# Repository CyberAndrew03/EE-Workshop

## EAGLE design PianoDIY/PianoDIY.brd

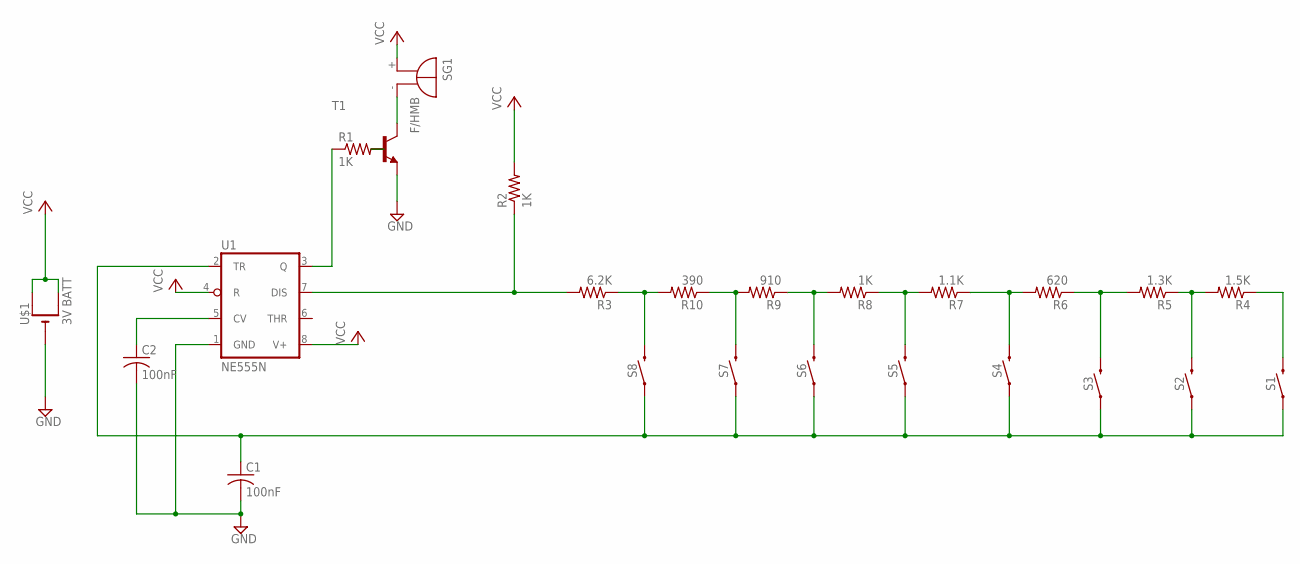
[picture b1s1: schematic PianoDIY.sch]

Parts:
C1, C2: 100nF; C025-025X050
R1, R2, R8: 1K; 0207/10
R3: 6.2K; 0207/10
R4: 1.5K; 0207/10
R5: 1.3K; 0207/10
R6: 620; 0207/10
R7: 1.1K; 0207/10
R9: 910; 0207/10
R10: 390; 0207/10
S1, S2, S3, S4, S5, S6, S7, S8: MOMENTARY-SWITCH-SPST-PTH-6.0MM; TACTILE_SWITCH_PTH_6.0MM
SG1: F/HMB
T1: -NPN-TO92-E1; TO92-E1
U1: NE555N; DIL08
U$1: 3V BATT; CR1220-THM

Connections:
GND: C1.2, C2.2, T1.3 (E), U1.1 (GND), U$1.-
unnamed: R2.1, R3.2, U1.7 (DIS)
unnamed: R3.1, R10.2, S8.3 (2)
unnamed: R9.2, R10.1, S7.3 (2)
unnamed: R8.2, R9.1, S6.3 (2)
unnamed: R7.2, R8.1, S5.3 (2)
unnamed: R6.2, R7.1, S4.3 (2)
unnamed: R5.2, R6.1, S3.3 (2)
unnamed: R4.2, R5.1, S2.3 (2)
unnamed: R4.1, S1.3 (2)
unnamed: C2.1, U1.5 (CV)
unnamed: R1.2, T1.2 (B)
unnamed: R1.1, U1.3 (Q)
unnamed: SG1.-, T1.1 (C)
unnamed: C1.1, S1.1, S2.1, S3.1, S4.1, S5.1, S6.1, S7.1, S8.1, U1.2 (TR)
VCC: R2.2, SG1.+, U1.4 (R), U1.8 (V+), U$1.+1 (+), U$1.+2 (+1)

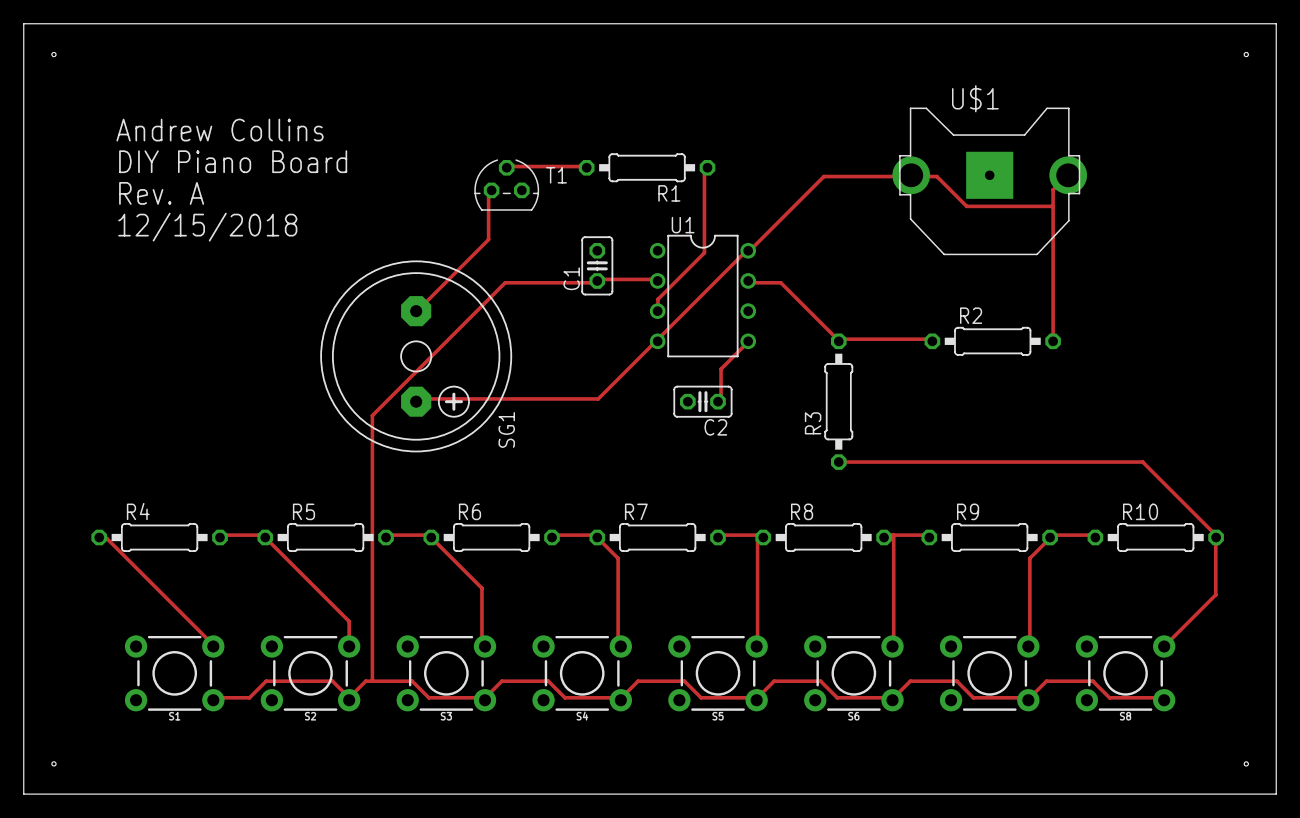
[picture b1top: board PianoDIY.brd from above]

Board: 2 copper layers, 105.4 x 64.8 mm, 24 parts (0 on the bottom side), 16 nets.

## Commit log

2018-12-01 .
    .
2018-12-08 Completed SCH
    .

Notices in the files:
parts and their libraries:
SparkFun-Switches: Licensing: Creative Commons ShareAlike 4.0 International - https://creativecommons.org/licenses/by-sa/4.0
